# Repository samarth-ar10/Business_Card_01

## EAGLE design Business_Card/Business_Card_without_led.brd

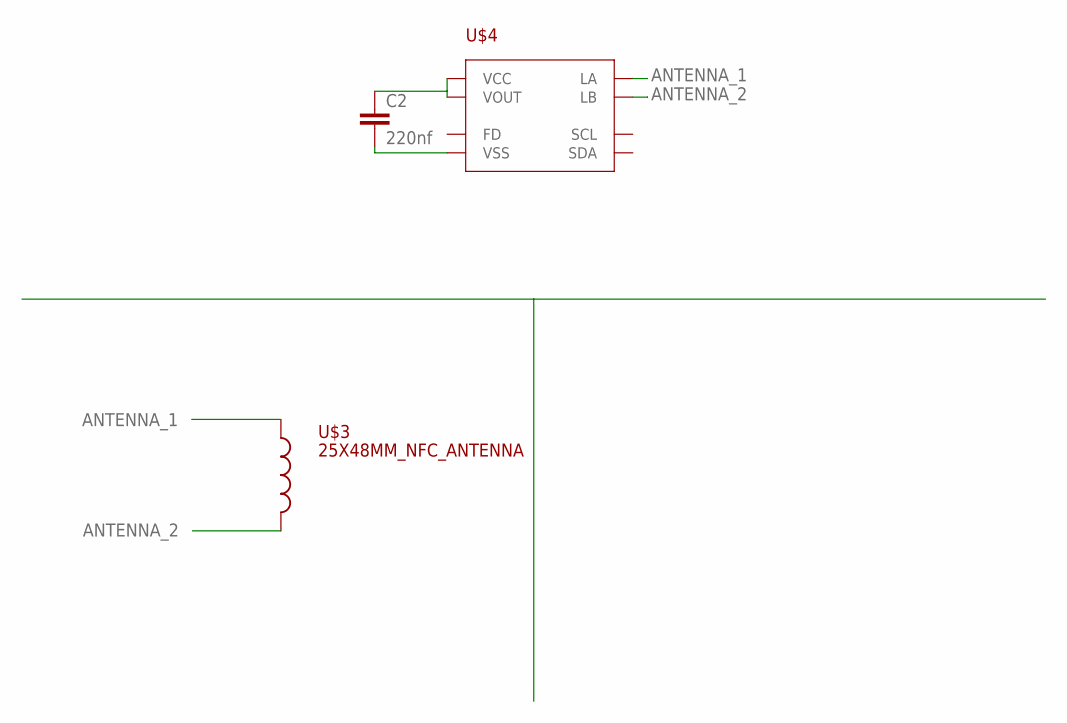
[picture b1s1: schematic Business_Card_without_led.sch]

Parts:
C2: 220nf; C0603
U$3: 25X48MM_NFC_ANTENNA
U$4: NT3H; XQFN8

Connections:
ANTENNA_1: U$3.P$1, U$4.LA
ANTENNA_2: U$3.P$2, U$4.LB
unnamed: C2.1, U$4.VCC, U$4.VOUT
unnamed: C2.2, U$4.VSS

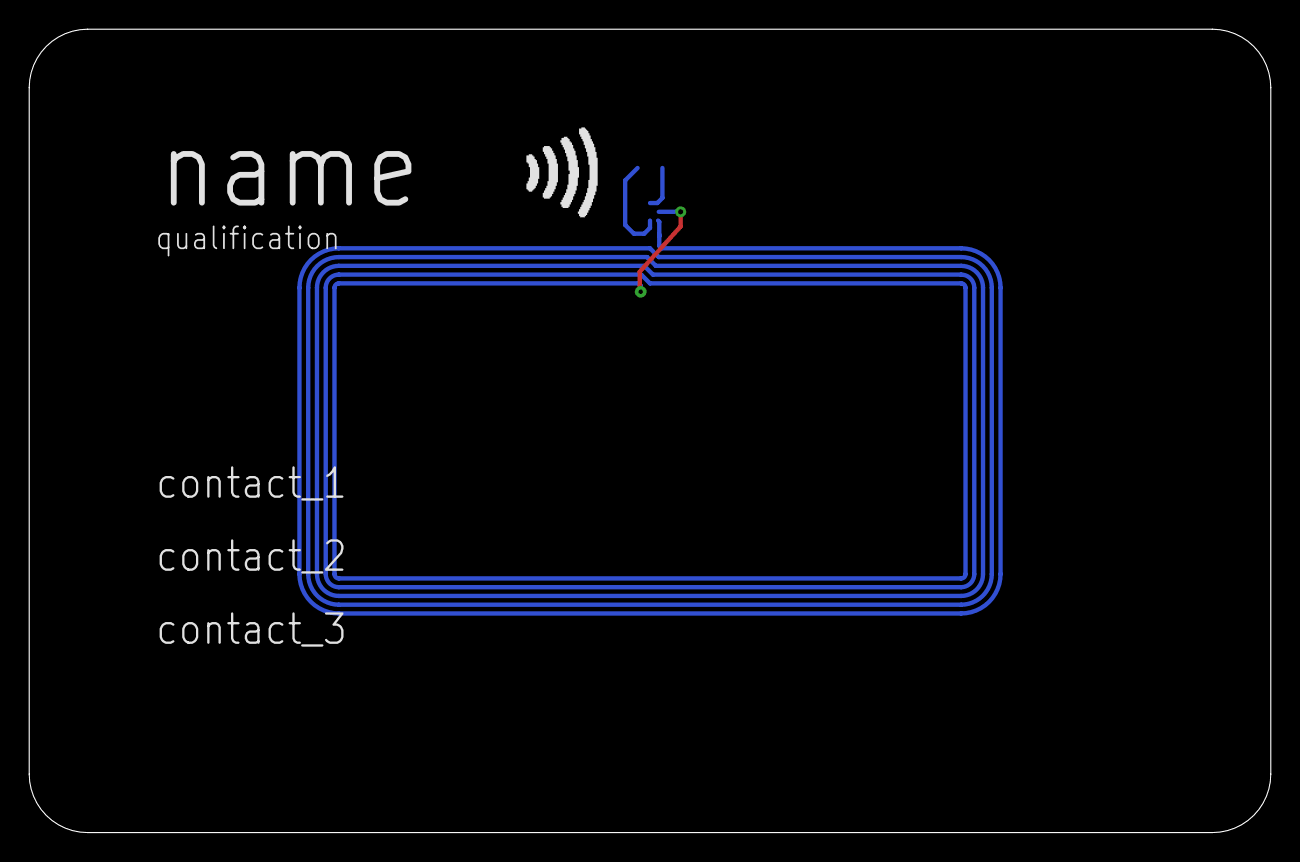
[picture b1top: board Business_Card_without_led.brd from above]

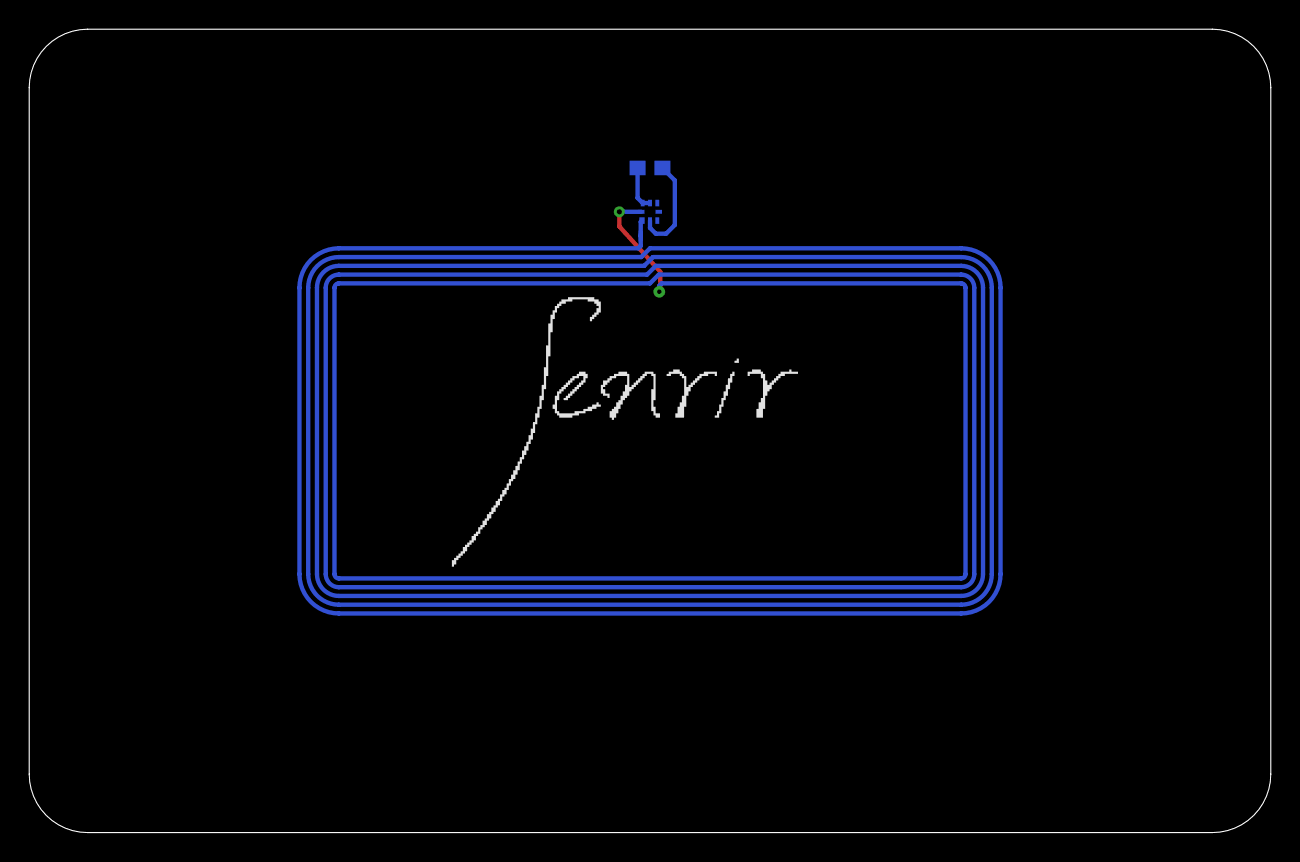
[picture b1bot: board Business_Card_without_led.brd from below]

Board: 2 copper layers, 85.0 x 55.0 mm, 3 parts (3 on the bottom side), 4 nets.

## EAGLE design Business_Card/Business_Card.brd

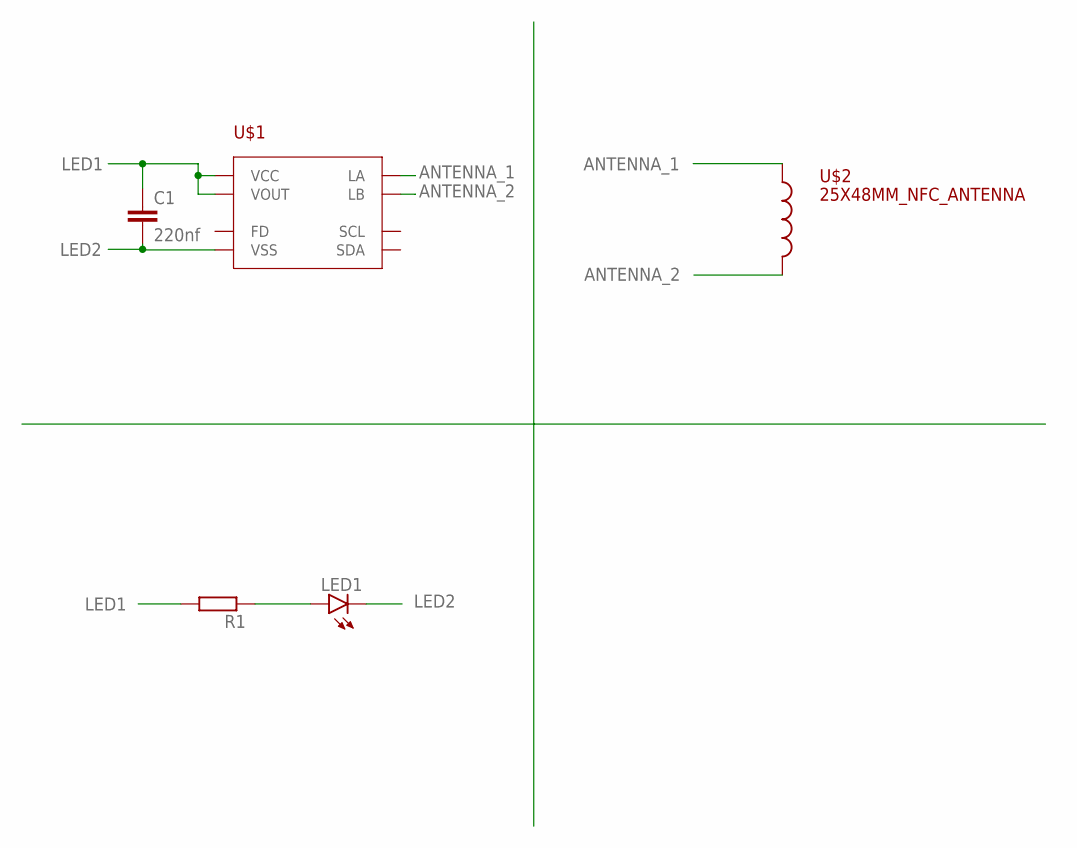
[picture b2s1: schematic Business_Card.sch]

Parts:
C1: 220nf; C0603
LED1: LEDCHIPLED_0805; CHIPLED_0805
R1: R-EU_R0603; R0603
U$1: NT3H; XQFN8
U$2: 25X48MM_NFC_ANTENNA

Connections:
ANTENNA_1: U$1.LA, U$2.P$1
ANTENNA_2: U$1.LB, U$2.P$2
LED1: C1.1, R1.2, U$1.VCC, U$1.VOUT
LED2: C1.2, LED1.C, U$1.VSS
unnamed: LED1.A, R1.1

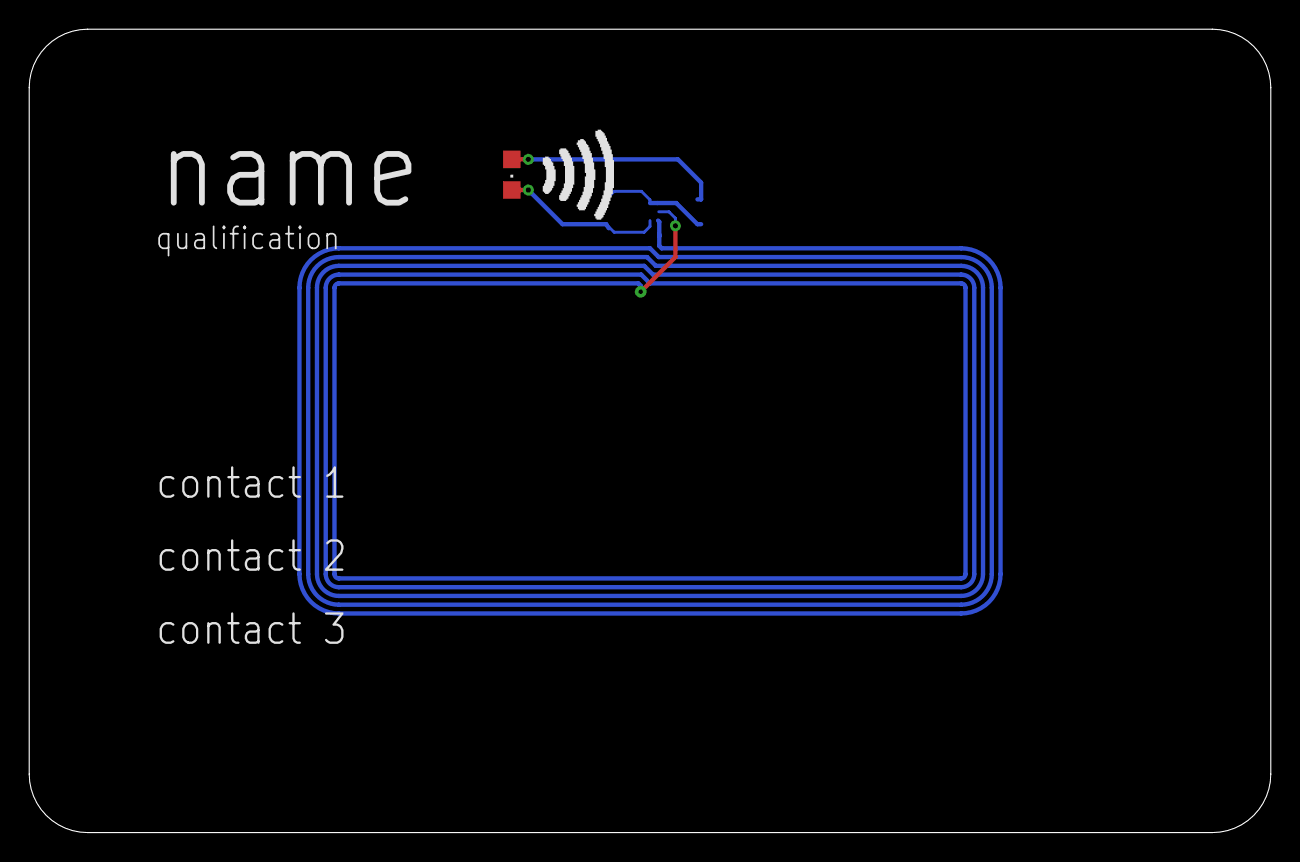
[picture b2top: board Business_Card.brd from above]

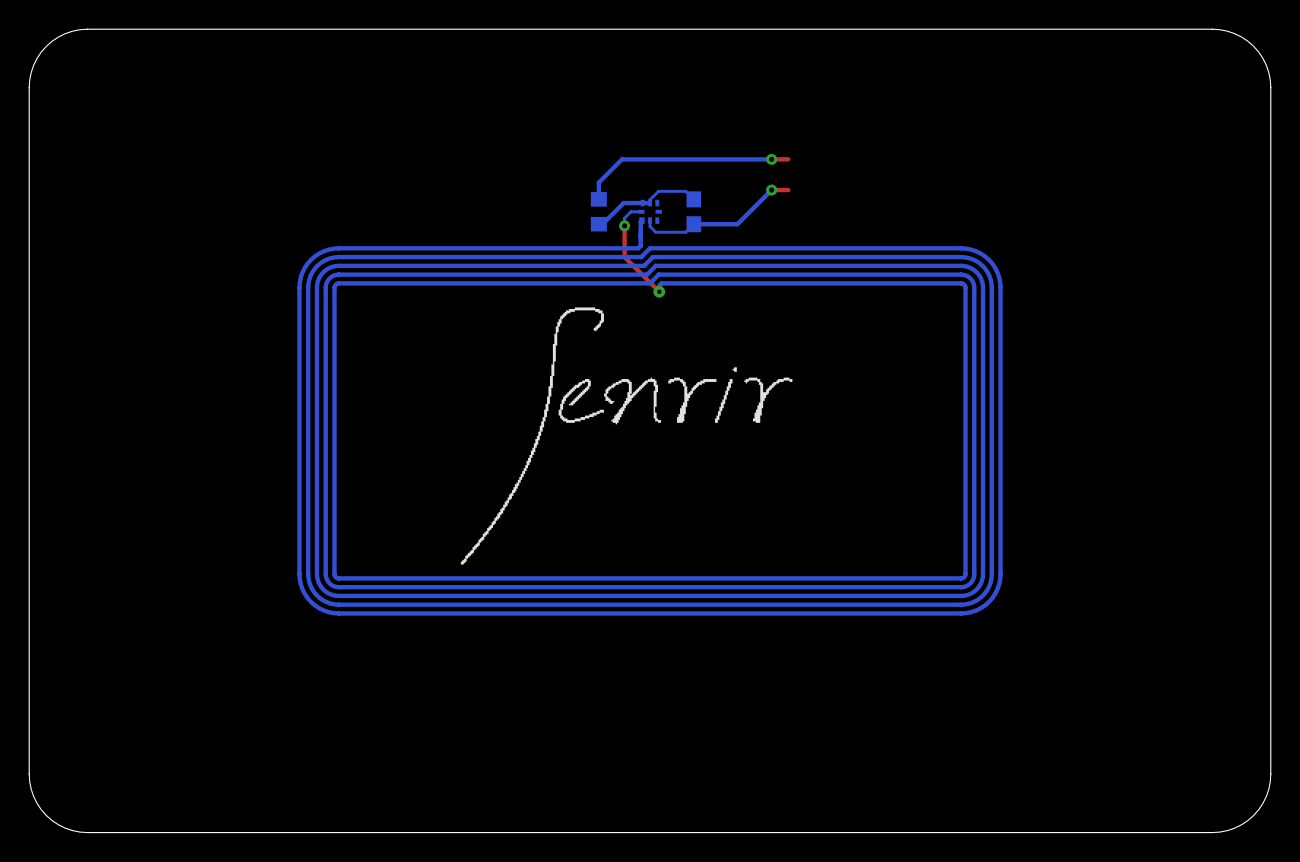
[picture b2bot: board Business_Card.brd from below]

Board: 2 copper layers, 85.0 x 55.0 mm, 5 parts (4 on the bottom side), 5 nets.

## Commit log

2020-01-30 local upload
2020-02-01 correcting for public use
2020-02-29 final submit for SAMARTH
2020-02-29 final edit for general
2020-03-15 adding brd image
2020-03-15 Adding Images
2020-11-09 Adding stl files
